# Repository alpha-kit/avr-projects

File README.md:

# avr-projects
Projects are based on 8-bit microcontrollers avr

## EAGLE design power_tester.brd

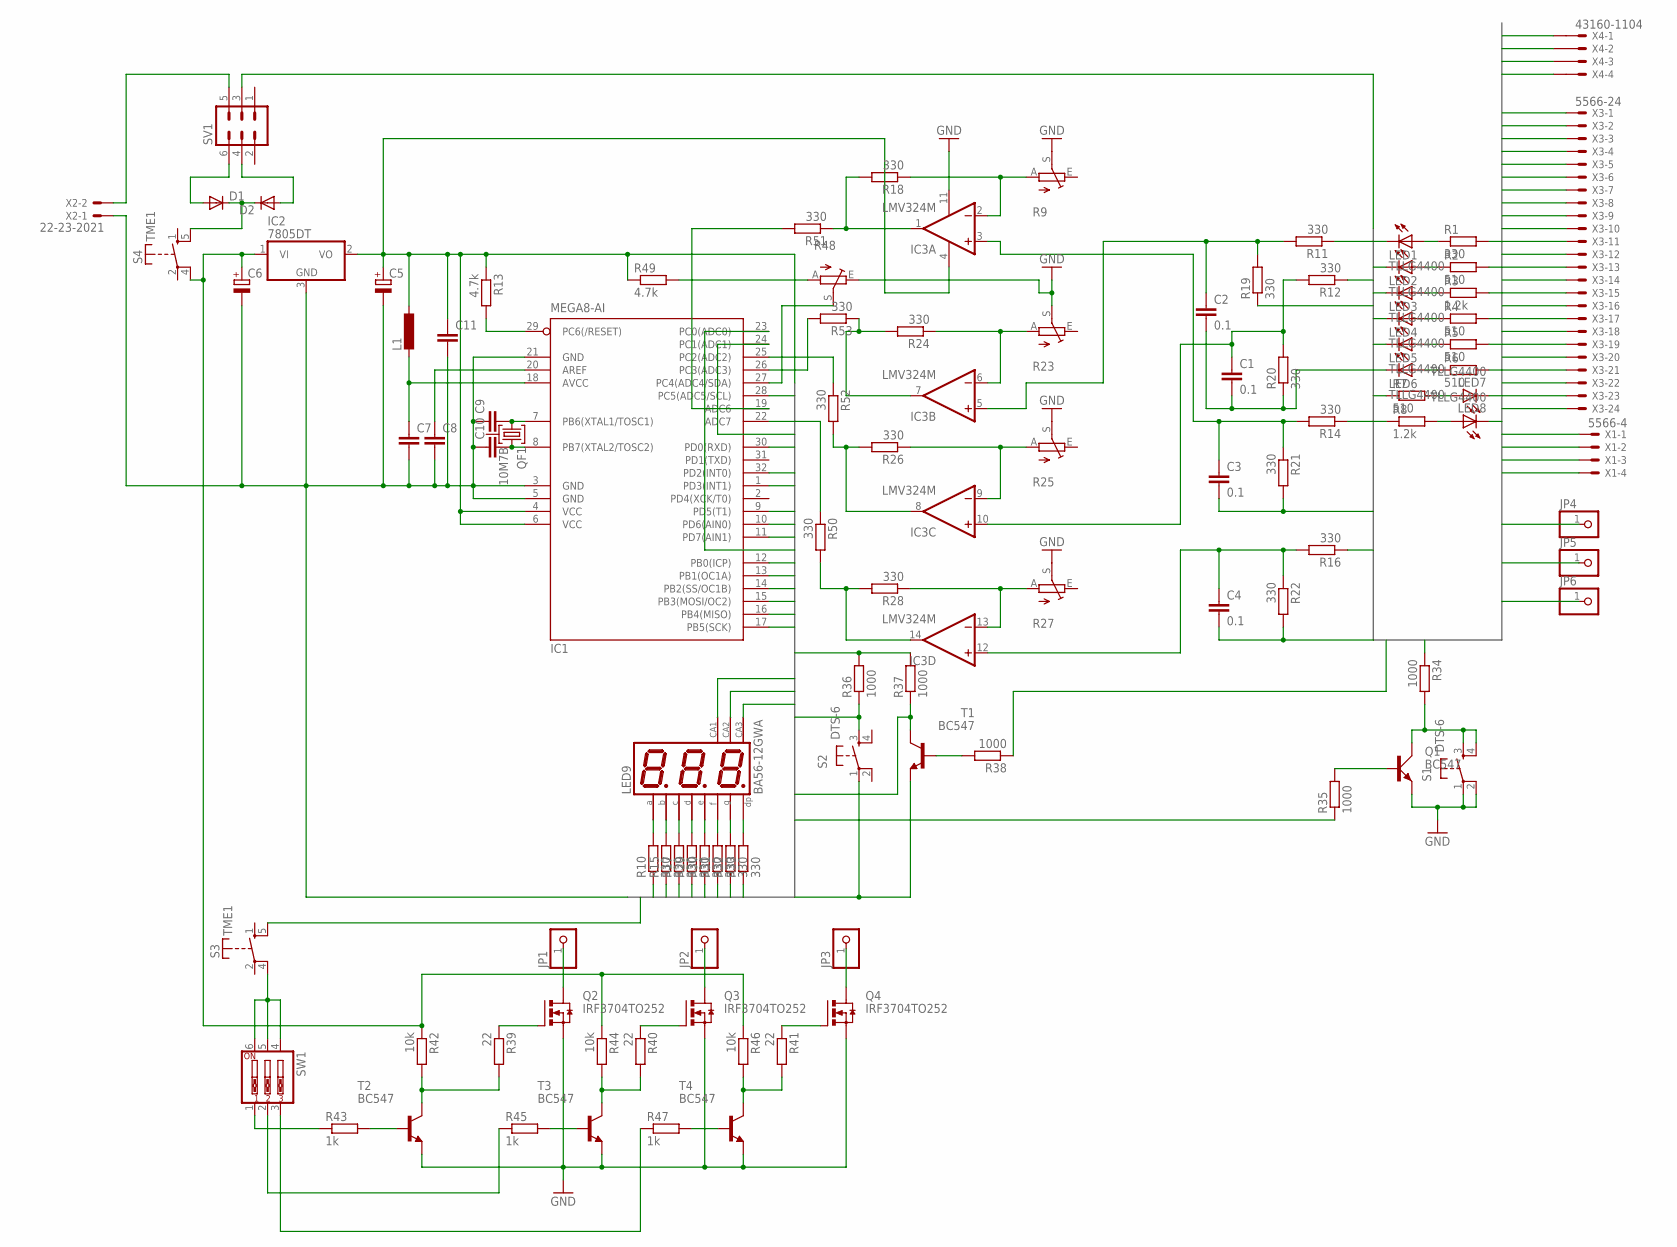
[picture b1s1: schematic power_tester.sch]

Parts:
C1, C2, C3, C4: 0.1; C1206
C5, C6: CPOL-EUE2.5-7; E2,5-7
C7, C9, C10, C11: C-EUC1206; C1206
C8: C-EUC0805K; C0805K
D1, D2: DIODE-DO214BA; DO214BA
IC1: MEGA8-AI; TQFP32-08
IC2: 7805DT; TO252
IC3: LMV324M; SO14
JP1, JP2, JP3, JP4, JP5, JP6: PINHD-1X1; 1X01
L1: DO3316P
LED1, LED2, LED3, LED4, LED5, LED6, LED7, LED8: TLLG4400; LED3MM
LED9: BA56-12GWA; BX56-12
Q1: BC547; SOT54A
Q2, Q3, Q4: IRF3704TO252; D-PAK_TO252AA
QF1: 10M7B; HC49U
R1, R11, R12, R14, R16, R17, R18, R19, R20, R21, R22, R24, R26, R28, R29, R30, R50, R52, R53: 330; R1206
R2, R4, R5, R6, R7: 510; R1206
R3, R8: 1.2k; R1206
R9, R23, R25, R27: TRIM_EU-S64W; S64W
R10, R15, R31, R32, R33, R51: 330; R1206W
R13: 4.7k; R1206W
R34, R38: 1000; R1206
R35, R36, R37: 1000; R1206W
R39, R40, R41: 22; R1206W
R42, R44, R46: 10k; R1206W
R43, R45, R47: 1k; R1206
R48: TRIM_EU-CA6V; CA6V
R49: 4.7k; R1206
S1, S2: DTS-6
S3, S4: TME1
SV1: MA03-2
SW1: SW_DIP-3; EDG-03
T1, T2, T3, T4: BC547; TO92
X1: 5566-4
X2: 22-23-2021
X3: 5566-24
X4: 43160-1104; 43160-XX04

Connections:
A: IC1.17 (PB5(SCK)), R10.1
B: IC1.16 (PB4(MISO)), R15.1
C: IC1.15 (PB3(MOSI/OC2)), R17.1
CA1: IC1.23 (PC0(ADC0)), LED9.12 (CA)
CA2: IC1.24 (PC1(ADC1)), LED9.9 (CA)
CA3: IC1.28 (PC5(ADC5/SCL)), LED9.8 (CA)
D: IC1.14 (PB2(SS/OC1B)), R29.1
DEGUR_5V: R6.2, R16.1, X3.9
DOWN_TO_ZERO: Q1.C, R34.2, S1.3, S1.4
DP: IC1.9 (PD5(T1)), R33.1
E: IC1.12 (PB0(ICP)), R30.1
F: IC1.11 (PD7(AIN1)), R31.1
G: IC1.10 (PD6(AIN0)), R32.1
GND: C1.2, C2.2, C3.2, C4.2, C5.-, C6.-, C7.2, C8.2, C9.1, C10.1, C11.2, IC1.3 (GND), IC1.5 (GND), IC1.21 (GND), IC2.3 (GND), IC3.11 (V-), LED1.K (C), LED2.K (C), LED3.K (C), LED4.K (C), LED5.K (C), LED6.K (C), Q1.E, Q2.4 (S), Q3.4 (S), Q4.4 (S), R7.1, R8.1, R9.S, R19.1, R20.1, R21.2, R22.2, R23.S, R25.S, R27.S, R48.E, S1.1, S1.2, S2.1, T1.1 (E), T2.1 (E), T3.1 (E), T4.1 (E), X1.1, X1.2, X2.1, X3.3, X3.5, X3.7, X3.15, X3.17, X3.18, X3.19, X3.24, X4.2@1, X4.3@1
LED_SWITCH: IC1.1 (PD3(INT1)), R36.1, S2.3
unnamed: LED1.A, R1.1
unnamed: LED3.A, R3.1
unnamed: LED2.A, R2.1
unnamed: LED4.A, R4.1
unnamed: LED5.A, R5.1
unnamed: LED6.A, R6.1
unnamed: LED7.A, R7.2
unnamed: LED8.A, R8.2
unnamed: IC1.29 (PC6(/RESET)), R13.2
unnamed: R39.2, R42.2, T2.3 (C)
unnamed: R40.2, R44.2, T3.3 (C)
unnamed: C3.1, IC3.3 (+IN), R14.2, R21.1
unnamed: IC3.2 (-IN), R9.A, R18.1
unnamed: C4.1, IC3.12 (+IN), R16.2, R22.1
unnamed: C2.1, IC3.5 (+IN), R11.2, R19.2
unnamed: C1.1, IC3.10 (+IN), R12.2, R20.2
unnamed: C9.2, IC1.7 (PB6(XTAL1/TOSC1)), QF1.1
unnamed: C10.2, IC1.8 (PB7(XTAL2/TOSC2)), QF1.3
unnamed: C6.+, IC2.1 (VI), R42.1, R44.1, R46.1, S4.4
unnamed: IC3.1 (OUT), R18.2, R51.1
unnamed: IC3.7 (OUT), R24.2, R53.1
unnamed: IC3.6 (-IN), R23.A, R24.1
unnamed: D1.A, SV1.6
unnamed: IC3.8 (OUT), R26.2, R52.2
unnamed: IC3.9 (-IN), R25.A, R26.1
unnamed: IC3.14 (OUT), R28.2, R50.2
unnamed: IC3.13 (-IN), R27.A, R28.1
unnamed: LED9.11 (A), R10.2
unnamed: D2.A, SV1.4
unnamed: LED9.7 (B), R15.2
unnamed: SV1.5, X2.2
unnamed: LED9.4 (C), R17.2
unnamed: C7.1, IC1.18 (AVCC), L1.1
unnamed: LED9.2 (D), R29.2
unnamed: LED9.1 (E), R30.2
unnamed: LED9.10 (F), R31.2
unnamed: LED9.5 (G), R32.2
unnamed: LED9.3 (DP), R33.2
unnamed: Q1.B, R35.2
unnamed: R38.2, T1.2 (B)
unnamed: R47.2, T4.2 (B)
unnamed: Q3.1 (G), R40.1
unnamed: Q4.1 (G), R41.1
unnamed: Q2.1 (G), R39.1
unnamed: R41.2, R46.2, T4.3 (C)
unnamed: R43.2, T2.2 (B)
unnamed: JP1.1, Q2.3 (D)
unnamed: JP2.1, Q3.3 (D)
unnamed: JP3.1, Q4.3 (D)
unnamed: R45.2, T3.2 (B)
unnamed: R48.A, R49.2
unnamed: R43.1, SW1.1
unnamed: R45.1, SW1.2
unnamed: R47.1, SW1.3
unnamed: S3.4, SW1.4, SW1.5, SW1.6
unnamed: IC1.27 (PC4(ADC4/SDA)), R48.S
unnamed: D1.C, D2.C, S4.5 (S)
unnamed: IC1.22 (ADC7), R50.1
unnamed: IC1.19 (ADC6), R51.2
unnamed: IC1.25 (PC2(ADC2)), R52.1
unnamed: IC1.26 (PC3(ADC3)), R53.2
unnamed: C8.1, IC1.20 (AREF)
PS_ON: R5.2, R34.1, X3.16
PS_ON_CONTROL: IC1.30 (PD0(RXD)), R35.1
PWN_LOAD: IC1.13 (PB1(OC1A)), S3.5 (S)
PWR_OK: R4.2, R38.1, X3.8
PWR_OK_CONTROL: IC1.32 (PD2(INT0)), R37.1, T1.3 (C)
VCC5V: C5.+, C11.1, IC1.4 (VCC), IC1.6 (VCC), IC2.2 (VO), IC3.4 (V+), L1.2, R13.1, R36.2, R37.2, R49.1
VDC3: JP4.1, R1.2, R14.1, X3.1, X3.2, X3.12, X3.13
VDC5: JP5.1, R2.2, R11.1, X3.4, X3.6, X3.21, X3.22, X3.23, X4.4@1
VDC12: JP6.1, R3.2, R12.1, SV1.3, X1.3, X1.4, X3.10, X3.11, X4.1@1
VDC-5: LED7.K (C), X3.20
VDC-12: LED8.K (C), X3.14

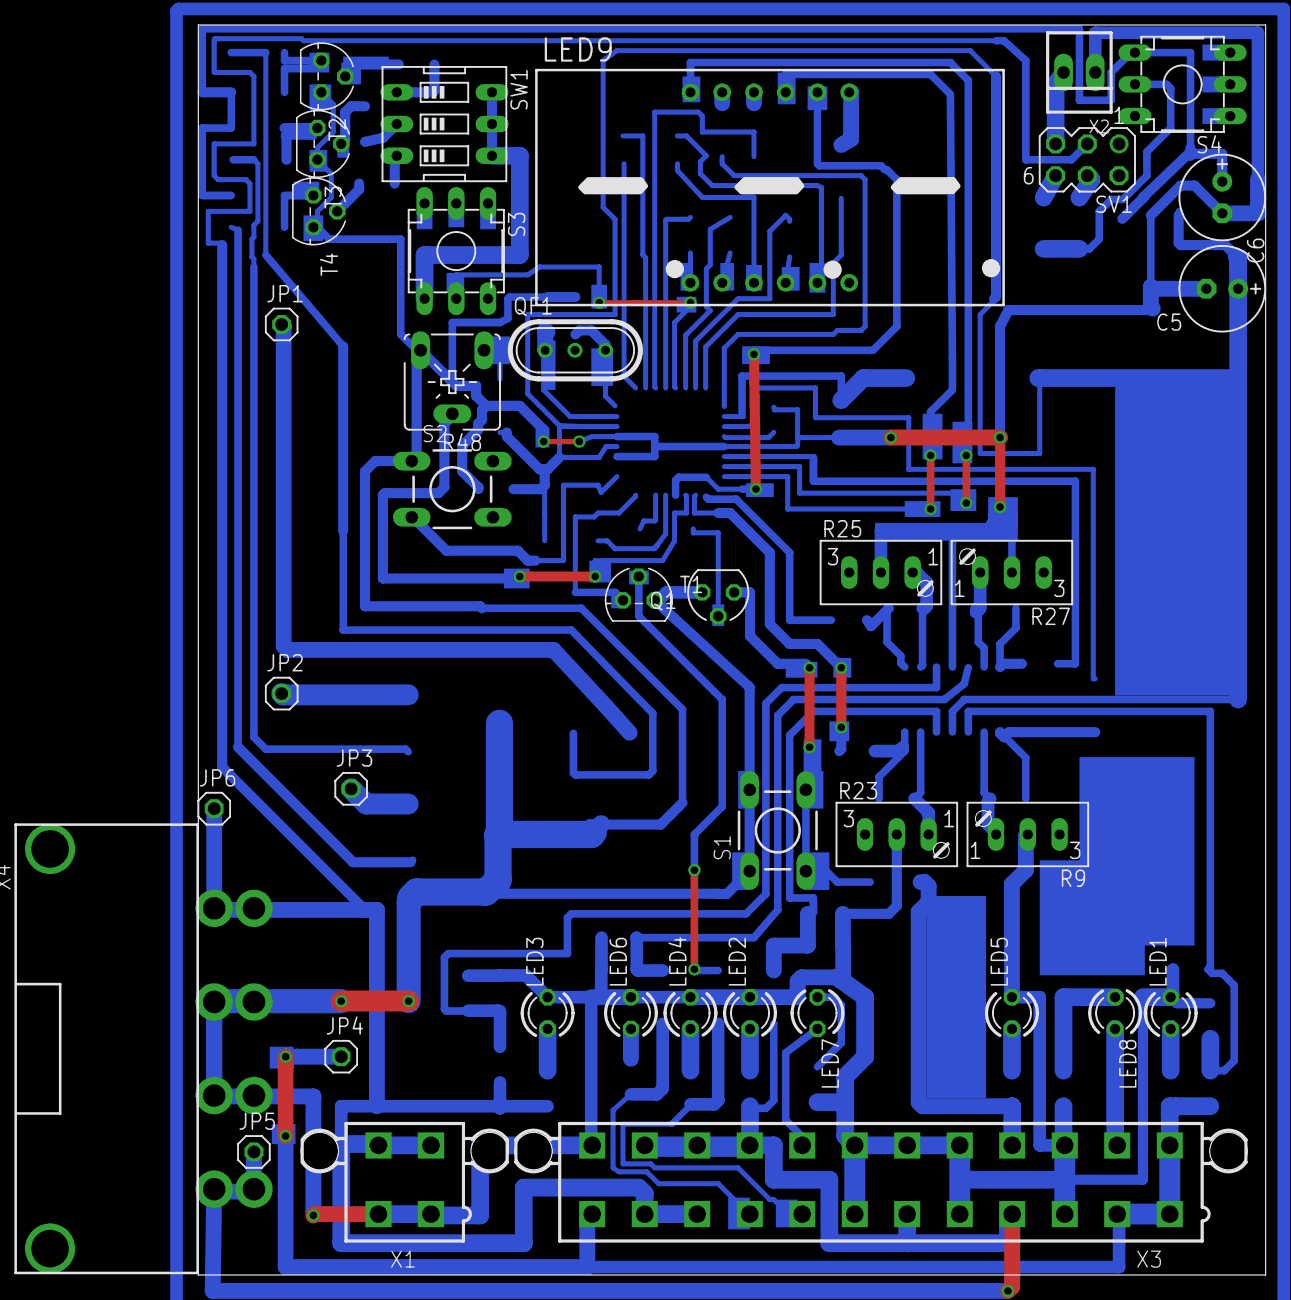
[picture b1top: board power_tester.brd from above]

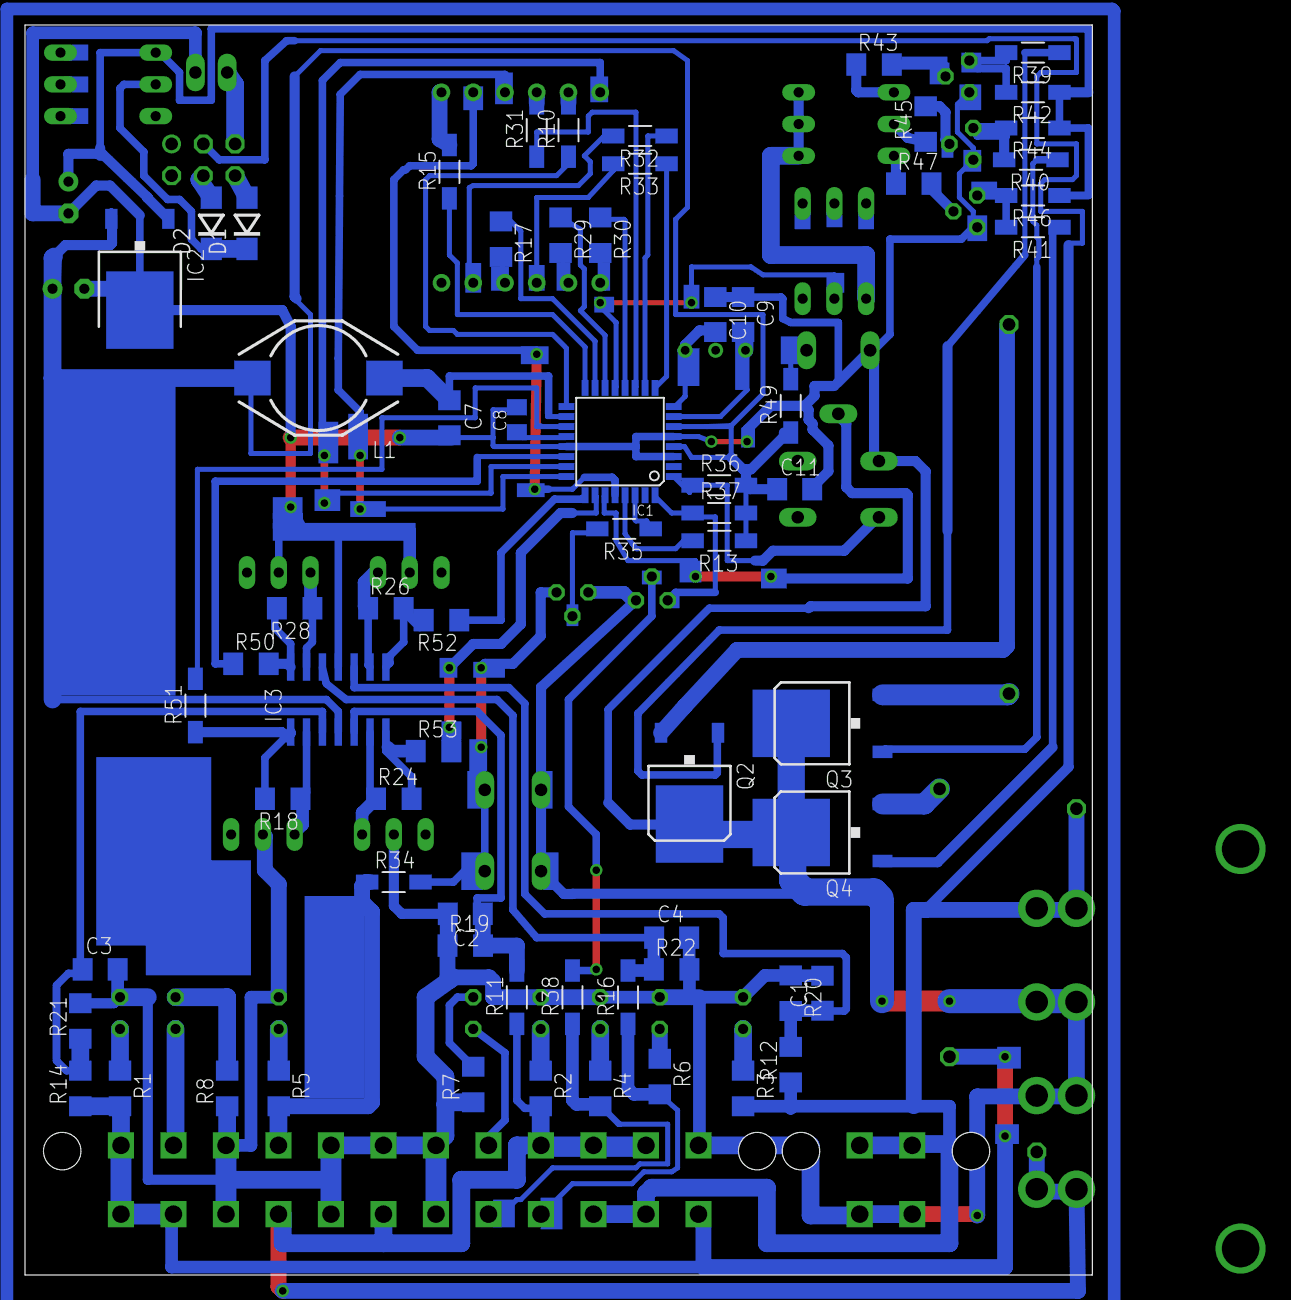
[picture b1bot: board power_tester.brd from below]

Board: 2 copper layers, 85.4 x 100.0 mm, 104 parts (66 on the bottom side), 88 nets.

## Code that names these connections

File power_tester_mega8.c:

#include <avr/io.h>
#include <avr/interrupt.h>

#define adc_3v ((1<<MUX2)|(1<<MUX1))
#define adc_5v ((1<<MUX1)|(1<<MUX0))
#define adc_12v (1<<MUX1)  
#define adc_degur_5v ((1<<MUX2)|(1<<MUX1)|(1<<MUX0))
#define adc_pwm_lvl (1<<MUX2)
#define adc_mux_clear 0b11110000

#define _3v 			0
#define _5v 			1
#define _12v 			2
#define _degur_5v 		3
#define _pwm_v			4
#define adc_max 		5


#define turn_ON_PS		0

#define PS_ON 0
#define PWR_OK 0

unsigned char voltage_array[5];
unsigned char adc_index=0;
unsigned char led_index=0;
unsigned char value_index=0;
unsigned char LED[3]={4,8,9};
unsigned char number_B[10]={
							0b11000000,//0
							0b11100101,//1
							0b11001000,//2
							0b11000001,//3
							0b11100101,//4
							0b11010001,//5
							0b11010000,//6
							0b11000101,//7
							0b11000000,//8
							0b11000001//9
							};
unsigned char number_D[10]={
							0b01111111,//0
							0b11111111,//1
							0b10111111,//2
							0b10111111,//3
							0b00111111,//4
							0b00111111,//5
							0b00111111,//6
							0b11111111,//7
							0b00111111,//8
							0b00111111//9
							};

unsigned char DP_D =0b11011111;


void init_GPIO()
{

	DDRC = 0b11100011;
	PORTC =0b11100011;

	DDRB = 0b11111111;
	PORTB = 0b00000000;

	DDRD = 0b11110111;
	PORTD = 0b11110000;

}
void change_adc_input(unsigned char input)
{
	switch (input)
	{
		case _3v : {
					ADMUX =  ADMUX & adc_mux_clear;//clear adc MUX
					ADMUX |= adc_3v;
					break;
					}
		case _5v : {
					ADMUX =  ADMUX & adc_mux_clear;//clear adc MUX
					ADMUX |= adc_5v;
					break;
					}
		case _12v : {
					ADMUX =  ADMUX & adc_mux_clear;//clear adc MUX
					ADMUX |= adc_12v;
					break;
					}
		case _degur_5v : {
							ADMUX =  ADMUX & adc_mux_clear;//clear adc MUX
							ADMUX |= adc_degur_5v;
							break;
							}
		case _pwm_v : {
						ADMUX =  ADMUX & adc_mux_clear;//clear adc MUX
						ADMUX |= adc_pwm_lvl;
						break;
						}
	}
}
void show_led_value()
{
	unsigned char tmp=0x00;
	tmp = PORTB;
	tmp= tmp&0b00000010;
	tmp = tmp|number_B[LED[led_index]];
//PORT B
	for (int i=0;i<8;i++)
	{
		if((tmp&0b00000001)==0x01)
		{
			PORTB |=(1<<i);
		}
		else
			{
				PORTB &=~(1<<i);
			}
			tmp = (tmp>>1);

	}
//port D
	if (led_index==0)
	{
		tmp = number_D[LED[led_index]];
		tmp=tmp&DP_D;
	}else
		{
			tmp = number_D[LED[led_index]];
		}
//port D
	tmp = (tmp>>6);
	for (int i=6;i<8;i++)
	{
		if((tmp&0b00000001)==0x01)
		{
			PORTD |=(1<<i);
		}
		else
			{
				PORTD &=~(1<<i);
			}
			tmp = (tmp>>1);

	}


	switch 	(led_index)
	{
		case 0:{
				
				PORTC &=~((1<<0)|(1<<1)|(1<<5));
				PORTC |=(1<<0);
				break;
				}
		case 1:{
				PORTC &=~((1<<0)|(1<<1)|(1<<5));
				PORTC |=(1<<1);
				break;
				}
		case 2:{
				PORTC &=~((1<<0)|(1<<1)|(1<<5));
				PORTC |=(1<<5);
				break;
				}
	}
	led_index++;
	if(led_index>=3){led_index=0;}


}
void init_timer_0()
{
	TCNT0=0x00;
//	TCCR0|=((1<<CS02)|(1<<CS01)|(1<<CS00)); //set prescaller 1024
	TIMSK|=(1<<TOIE0);
	TCCR0|=(1<<CS00)|(1<<CS01);
//TCCR0|=(1<<CS01);
}

void init_measuring_timer_1()
{
	TCNT1=0x00;
}


void init_adc()
{
	ADMUX|=((1<<REFS1)|(1<<REFS0));// internal 2.56
	//ADMUX|=(1<<REFS0);//  external AVCC
	ADMUX|=(1<<ADLAR);// shift left

	ADCSRA|=((1<<ADIE)|(1<<ADEN)|(1<<ADPS2)|(1<<ADPS1)|(1<<ADPS0)); // ENABLE ADC, ENABLE ADC INTERRUPT, SET PRESCALER 128
	
	ADMUX =  ADMUX & adc_mux_clear;//clear adc MUX
}

ISR (ADC_vect)
{
	cli();
	//adc_data[adc_counter]=ADCH;
	//adc_counter++;
//	ADCSRA|=(1<<ADSC);
	sei();
	//uart_transmit(ADCH);
	voltage_array[0]=1;
}

ISR(INT1_vect)
{
cli();
	unsigned int temp;
	temp = ((voltage_array[value_index]*256)/256);
	LED[0] = temp /100;
	temp = temp %100;
	LED[1] = temp/10;
	LED[2] = temp%10;

		value_index++;	
	if(value_index>5){value_index=0;}
sei();
}

ISR(INT0_vect)
{
}

ISR (TIMER0_OVF_vect)
{
	//PORTB= 0xff;
	cli();
	change_adc_input(adc_index);
	if(adc_index<adc_max)
	{
		adc_index++;
	}else
		{
			adc_index=0;
		}
	show_led_value();
	sei();
	
}
void init_interrupt()
{
	GICR|=((1<<INT1)|(1<<INT0));
	MCUCR|=((1<<ISC11)|(1<<ISC01));
}

int main ()
{
	init_GPIO();
	 init_interrupt();
	 init_adc();
	 init_timer_0();
	sei();
	
	PORTD |= (1<<turn_ON_PS);
	
	while(1)
	{
		//PORTC=PORTC;
		
	}
}

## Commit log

2015-09-01 electric circuit + pcb board
    power tester for PC power supply ATX-24 pin
2015-09-14 change
    change
